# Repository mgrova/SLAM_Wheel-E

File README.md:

# SLAM_Wheel-E
Este es un proyecto en el cual se busca realizar una comparativa de diferentes técnicas de SLAM empleando un robot movil diferencial tipo Rover.

# Wheel-E 

Un análisis en detalle de todo el proyecto, así como de sus resultados se encuentra (en español) [aquí](doc.md). Los recursos bibliográficos disponibles se pueden consultar en [docs/](SLAM_Wheel-E/docs/). 

# DEPENDENCIAS
## Uso de lod gpio de la RPi
Se hace uso de la libreria pigpio:(http://abyz.me.uk/rpi/pigpio/download.html)

```
wget abyz.me.uk/rpi/pigpio/pigpio.tar
tar xf pigpio.tar
cd PIGPIO
make
sudo make install
```

## Comunicación Serial RPi-Arduino
Se hará uso de la librería de Python:

https://github.com/harmsm/PyCmdMessenger

Destacar que se emplará python2.7 y no python3.

## Comunicación multimaster(https://wiki.ros.org/multimaster_fkie)
Para comunicar la RPi y el PC, es necesario tener instalado el siguiente paquete:

```
sudo apt install ros-kinetic-multimaster-fkie
sudo apt install ros-kinetic-multimaster-launch
```

## Drivers Kinect v1 (RGB-D Camera)
Se emplearán tanto los driver necesarios para leer la IMU de la cámara y mover su motor cómo los que permiten que se pueda correr la cámara.

 - Drivers Cámara principales
```
sudo apt install ros-kinetic-freenect-stack<
```

 - Driver IMU y motor de la cámara(https://wiki.ros.org/kinect_aux)
```
sudo apt-get install libusb-1.0-0 libusb-1.0-0-dev
```
```
cd ~/catkin_ws/src
git clone https://github.com/muhrix/kinect_aux.git -b indigo
cd ~/catkin_ws
catkin_make
```

## RTAB-Map SLAM
Se deberan tener instalados los siguientes paquetes de ros y sus respectivas dependencias:
```
sudo apt-get install ros-kinetic-rtabmap-ros
sudo apt-get install ros-kinetic-octomap-*

```

## ORB-SLAM2
Se enlaza directamente al repositorio original.
https://github.com/appliedAI-Initiative/orb_slam_2_ros

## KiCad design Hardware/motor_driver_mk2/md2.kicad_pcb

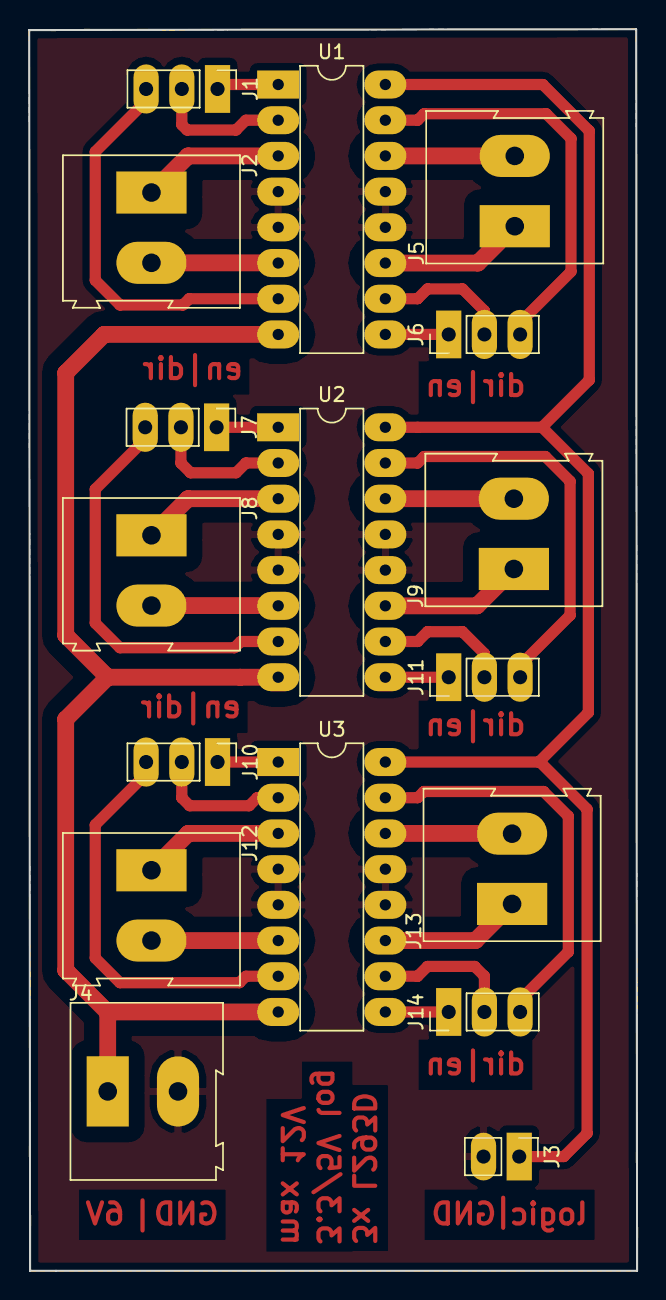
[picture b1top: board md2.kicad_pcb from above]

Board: 2 copper layers, 43.2 x 88.3 mm, 17 parts (0 on the bottom side), 32 nets.

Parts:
J1, J7, J10: mode&en M1; Pin_Header_Straight_1x03_Pitch2.54mm
J2, J8, J12: M1; TerminalBlock_Altech_AK300-2_P5.00mm
J3: Logic supply voltage; Pin_Header_Straight_1x02_Pitch2.54mm
J4: Power supply voltage; TerminalBlock_Altech_AK300-2_P5.00mm
J5, J9, J13: M2; TerminalBlock_Altech_AK300-2_P5.00mm
J6, J11, J14: mode&en M2; Pin_Header_Straight_1x03_Pitch2.54mm
U1, U2, U3: L293D; DIP-16_W7.62mm_LongPads

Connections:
/en1: J1.1, U1.1
/en2: J6.1, J14.1, U1.9, U3.9
/en12: J7.1, U2.1
/en13: J10.1, U3.1
/en22: J11.1, U2.9
/m1+: J2.1, U1.3
/m1+2: J8.1, U2.3
/m1+3: J12.1, U3.3
/m1-: J2.2, U1.6
/m1-2: J8.2, U2.6
/m1-3: J12.2, U3.6
/m2+: J5.1, U1.11
/m2+2: J9.1, U2.11
/m2+3: J13.1, U3.11
/m2-: J5.2, U1.14
/m2-2: J9.2, U2.14
/m2-3: J13.2, U3.14
/mode1+: J1.2, U1.2
/mode1+2: J7.2, U2.2
/mode1+3: J10.2, U3.2
/mode1-: J1.3, U1.7
/mode1-2: J7.3, U2.7
/mode1-3: J10.3, U3.7
/mode2+: J6.2, U1.10
/mode2+2: J11.2, U2.10
/mode2+3: J14.2, U3.10
/mode2-: J6.3, U1.15
/mode2-2: J11.3, U2.15
/mode2-3: J14.3, U3.15
GND: J3.2, J4.2, U1.4, U1.5, U1.12, U1.13, U2.4, U2.5, U2.12, U2.13, U3.4, U3.5, U3.12, U3.13
ardu5v: J3.1, U1.16, U2.16, U3.16
supply: J4.1, U1.8, U2.8, U3.8

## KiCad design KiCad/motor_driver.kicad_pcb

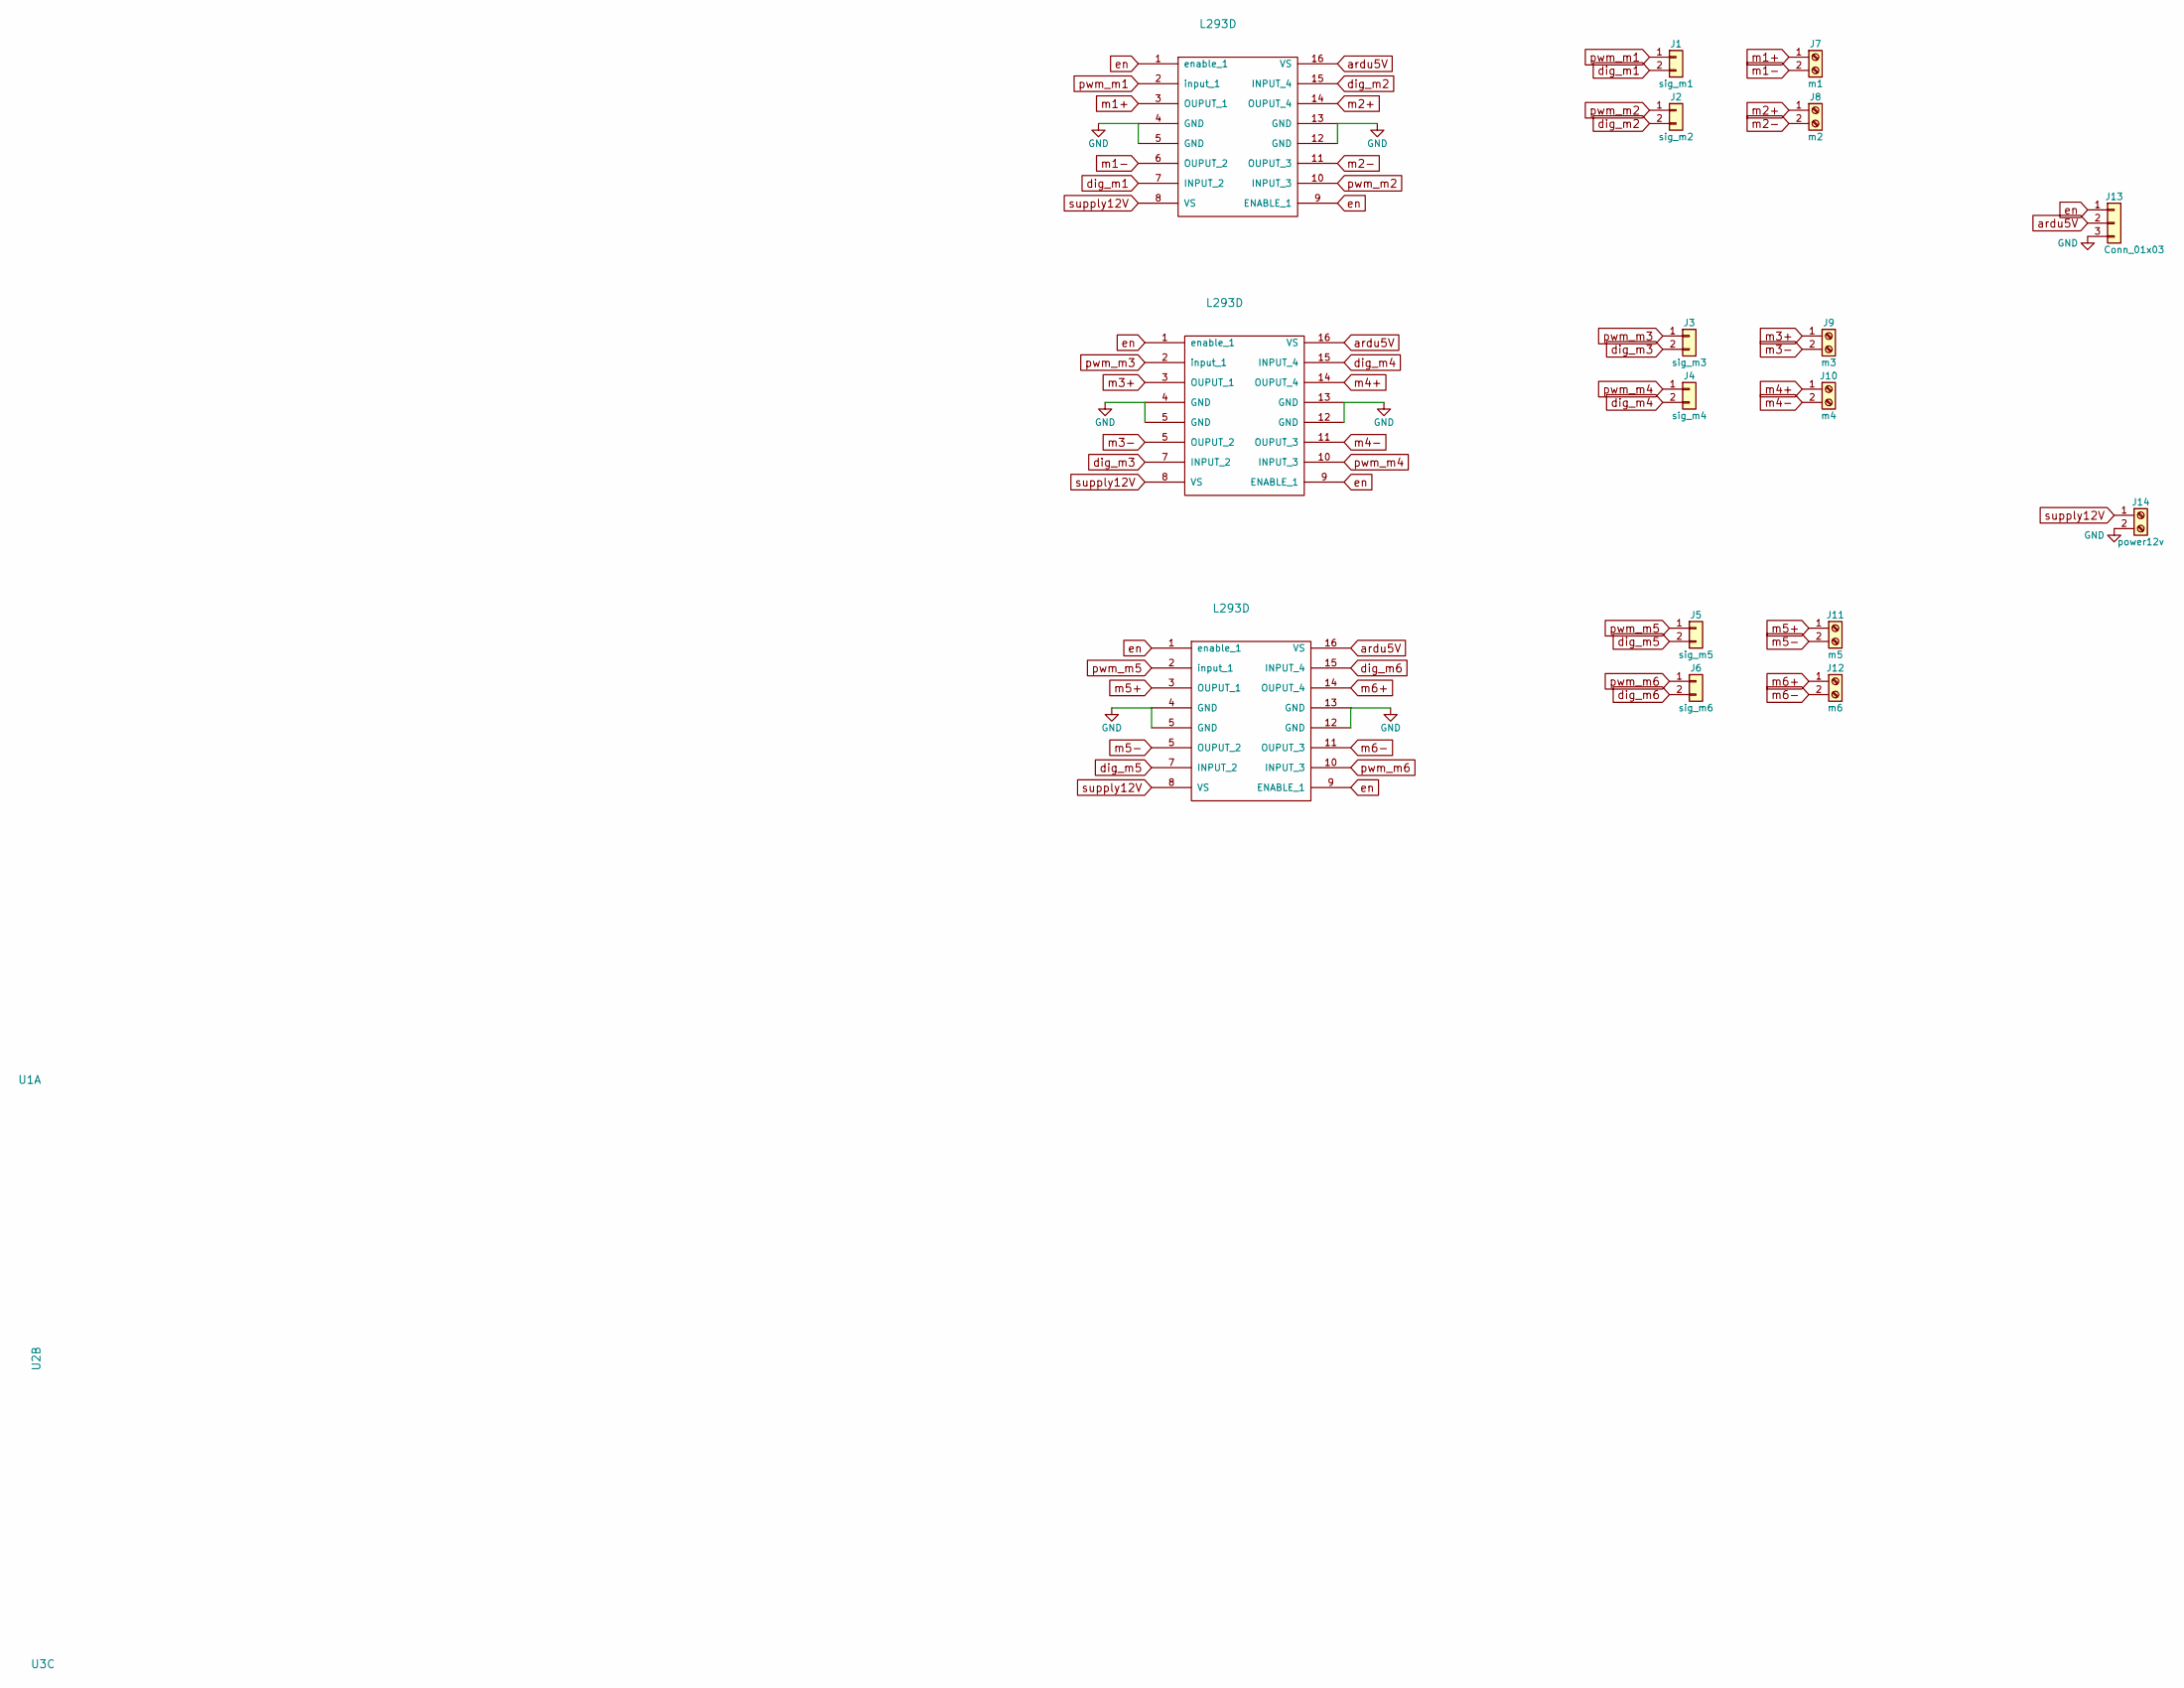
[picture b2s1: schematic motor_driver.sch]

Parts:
J1: sig_m1; Pin_Header_Straight_1x02_Pitch2.00mm
J2: sig_m2; Pin_Header_Straight_1x02_Pitch2.00mm
J3: sig_m3; Pin_Header_Straight_1x02_Pitch2.00mm
J4: sig_m4; Pin_Header_Straight_1x02_Pitch2.00mm
J5: sig_m5; Pin_Header_Straight_1x02_Pitch2.00mm
J6: sig_m6; Pin_Header_Straight_1x02_Pitch2.00mm
J7: m1; TerminalBlock_Altech_AK300-2_P5.00mm
J8: m2; TerminalBlock_Altech_AK300-2_P5.00mm
J9: m3; TerminalBlock_Altech_AK300-2_P5.00mm
J10: m4; TerminalBlock_Altech_AK300-2_P5.00mm
J11: m5; TerminalBlock_Altech_AK300-2_P5.00mm
J12: m6; TerminalBlock_Altech_AK300-2_P5.00mm
J13: Conn_01x03; Pin_Header_Straight_1x03_Pitch2.00mm
J14: power12v; TerminalBlock_Altech_AK300-2_P5.00mm
U1, U2, U3: L293D; DIP-16_W7.62mm_Socket_LongPads

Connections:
ardu5V: J13.2, U1.16 (VS), U2.16 (VS), U3.16 (VS)
dig_m1: J1.2, U1.7 (INPUT_2)
dig_m2: J2.2, U1.15 (INPUT_4)
dig_m3: J3.2, U2.7 (INPUT_2)
dig_m4: J4.2, U2.15 (INPUT_4)
dig_m5: J5.2, U3.7 (INPUT_2)
dig_m6: J6.2, U3.15 (INPUT_4)
en: J13.1, U1.1 (enable_1), U1.9 (ENABLE_1), U2.1 (enable_1), U2.9 (ENABLE_1), U3.1 (enable_1), U3.9 (ENABLE_1)
m1+: J7.1, U1.3 (OUPUT_1)
m1-: J7.2, U1.6 (OUPUT_2)
m2+: J8.1, U1.14 (OUPUT_4)
m2-: J8.2, U1.11 (OUPUT_3)
m3+: J9.1, U2.3 (OUPUT_1)
m4+: J10.1, U2.14 (OUPUT_4)
m4-: J10.2, U2.11 (OUPUT_3)
m5+: J11.1, U3.3 (OUPUT_1)
m6+: J12.1, U3.14 (OUPUT_4)
m6-: J12.2, U3.11 (OUPUT_3)
pwm_m1: J1.1, U1.2 (input_1)
pwm_m2: J2.1, U1.10 (INPUT_3)
pwm_m3: J3.1, U2.2 (input_1)
pwm_m4: J4.1, U2.10 (INPUT_3)
pwm_m5: J5.1, U3.2 (input_1)
pwm_m6: J6.1, U3.10 (INPUT_3)
supply12V: J14.1, U1.8 (VS), U2.8 (VS), U3.8 (VS)

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
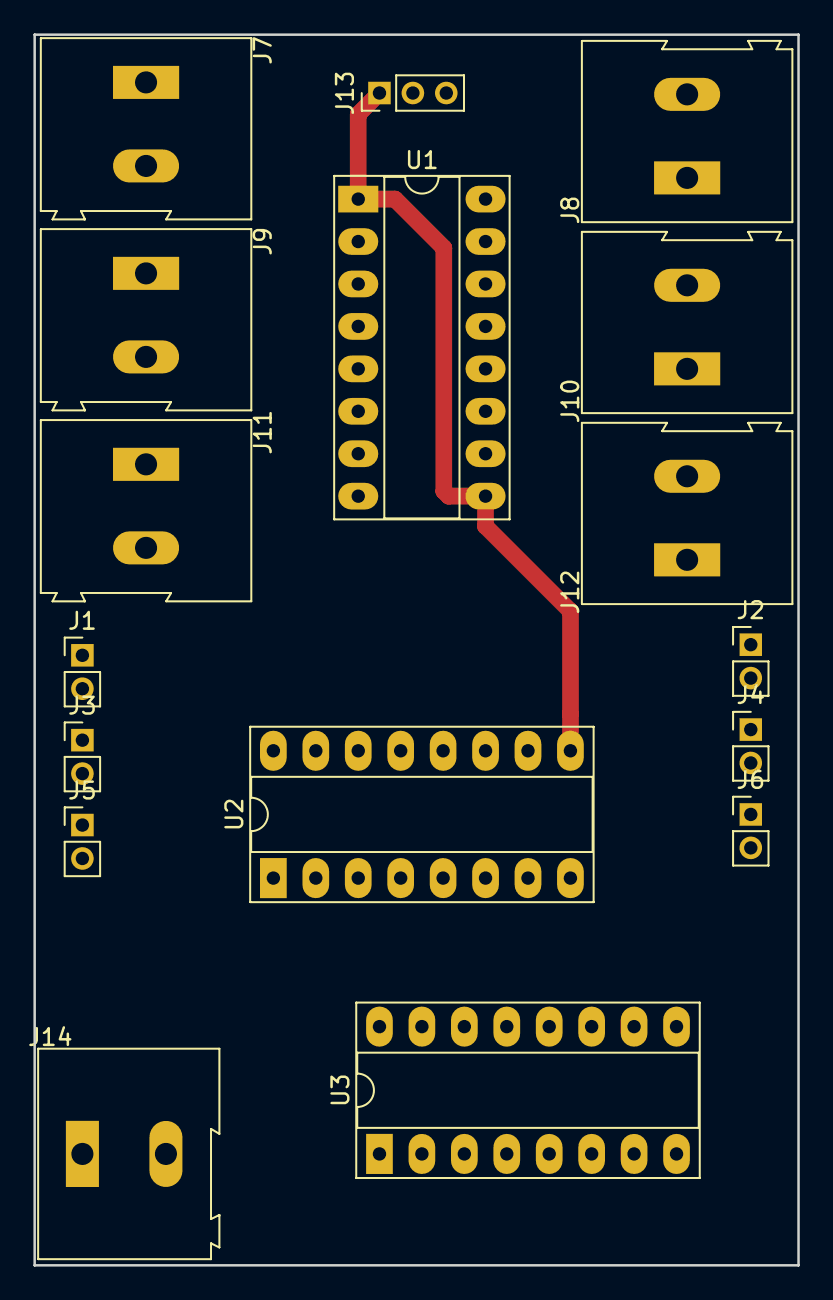
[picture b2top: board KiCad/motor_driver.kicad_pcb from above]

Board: 2 copper layers, 45.7 x 73.7 mm, 17 parts (0 on the bottom side), 28 nets.

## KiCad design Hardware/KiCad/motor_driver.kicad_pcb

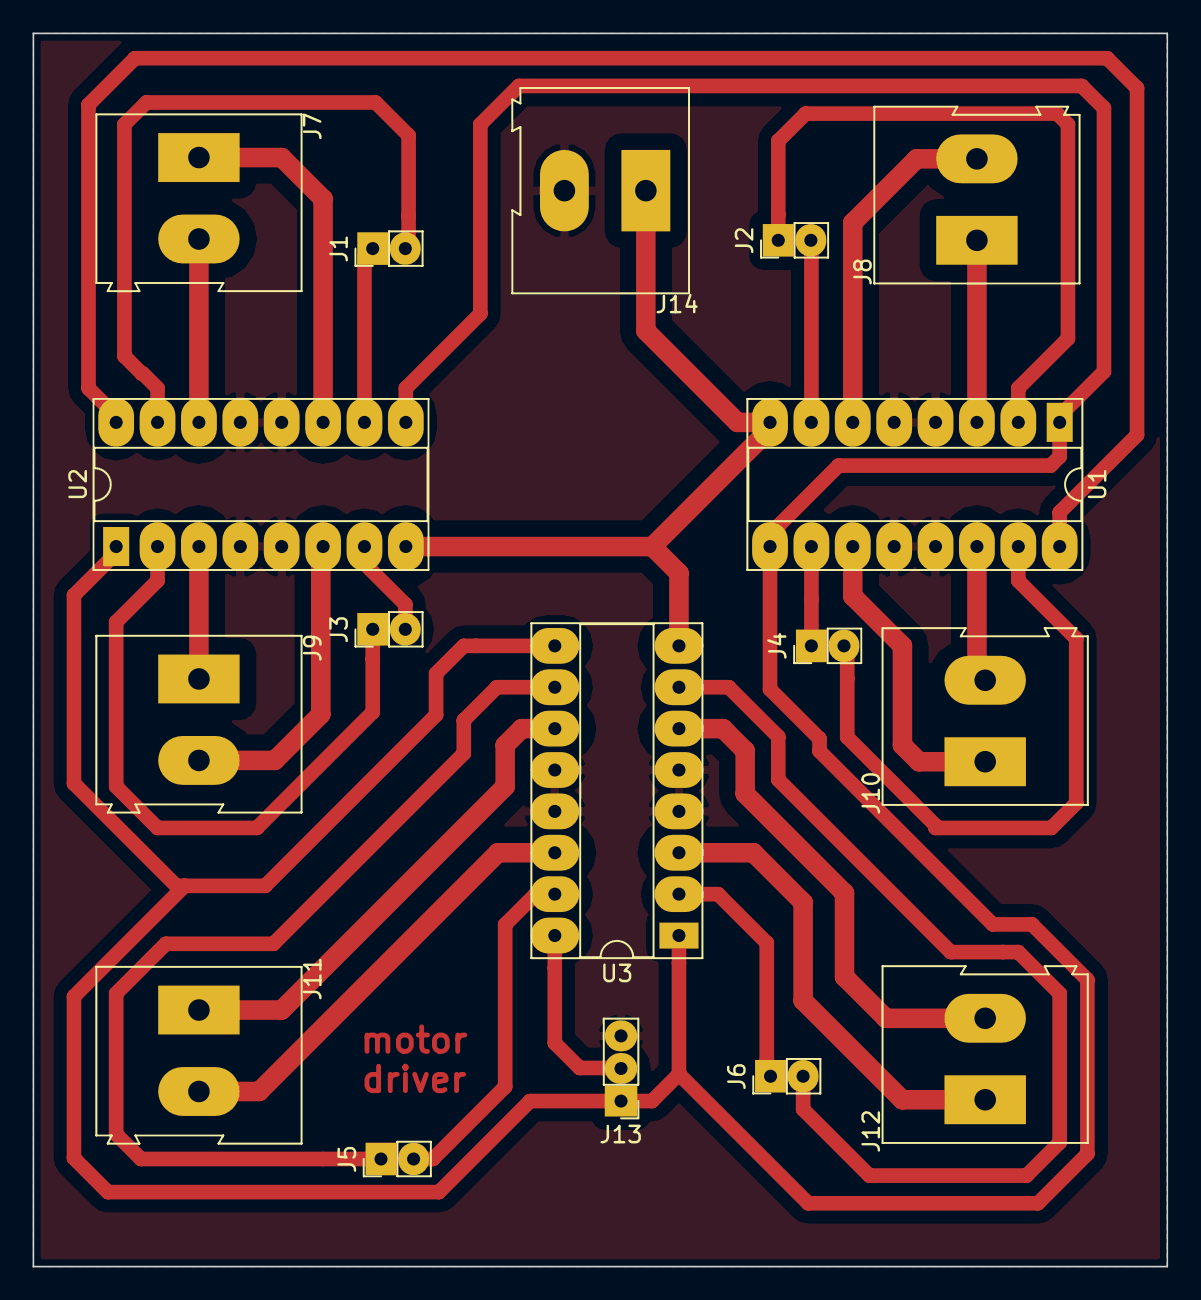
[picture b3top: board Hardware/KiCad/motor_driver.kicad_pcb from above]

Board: 2 copper layers, 69.6 x 75.7 mm, 17 parts (0 on the bottom side), 28 nets.

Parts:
J1, J2, J3, J4, J5, J6: Conn_01x02; Pin_Header_Straight_1x02_Pitch2.00mm
J7: m1; TerminalBlock_Altech_AK300-2_P5.00mm
J8: m2; TerminalBlock_Altech_AK300-2_P5.00mm
J9: m3; TerminalBlock_Altech_AK300-2_P5.00mm
J10: m4; TerminalBlock_Altech_AK300-2_P5.00mm
J11: m5; TerminalBlock_Altech_AK300-2_P5.00mm
J12: m6; TerminalBlock_Altech_AK300-2_P5.00mm
J13: Conn_01x03; Pin_Header_Straight_1x03_Pitch2.00mm
J14: power12v; TerminalBlock_Altech_AK300-2_P5.00mm
U1, U2, U3: L293D; DIP-16_W7.62mm_Socket_LongPads

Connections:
GND: J13.3, J14.2, U1.4, U1.5, U1.12, U1.13, U2.4, U2.5, U2.12, U2.13, U3.4, U3.5, U3.12, U3.13
ardu5V: J13.2, U1.16, U2.16, U3.16
dig_m1: J1.2, U2.15
dig_m2: J2.2, U1.7
dig_m3: J3.2, U2.7
dig_m4: J4.2, U1.15
dig_m5: J5.2, U3.15
dig_m6: J6.2, U3.7
en: J13.1, U1.1, U1.9, U2.1, U2.9, U3.1, U3.9
m1+: J7.1, U2.11
m1-: J7.2, U2.14
m2+: J8.1, U1.3
m2-: J8.2, U1.6
m3+: J9.1, U2.3
m3-: J9.2, U2.6
m4+: J10.1, U1.11
m4-: J10.2, U1.14
m5+: J11.1, U3.11
m5-: J11.2, U3.14
m6+: J12.1, U3.3
m6-: J12.2, U3.6
pwm_m1: J1.1, U2.10
pwm_m2: J2.1, U1.2
pwm_m3: J3.1, U2.2
pwm_m4: J4.1, U1.10
pwm_m5: J5.1, U3.10
pwm_m6: J6.1, U3.2
supply12V: J14.1, U1.8, U2.8, U3.8

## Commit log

2019-02-24 Anadido el fichero con el analisis de los diferentes metodos de slam. Tambien los datasets para slam RGB-D
2019-02-24 pcb driver motor
2019-02-24 Datasheet L293D
2019-02-25 diy l293d design in kicad
2019-02-25 one f*** layer pcb finished, with just 3 bridges
2019-02-28 Added arduino files to control motors
2019-02-28 Added RPi node to control motors with freenet launch
2019-03-01 Modified PCB and added link to txt
2019-03-01 motor driver pcb mkII
2019-03-01 added text
2019-03-01 added robot in freecad base
2019-03-01 added gitignore
2019-03-06 Motor driver mk2 pcb
2019-03-06 Added backup
2019-03-06 soldad esto si hay huevos
2019-03-08 holi
2019-03-08 added face robot to freecad filesystem and dc motors "datasheet". In slam methods octomap
2019-03-08 added arduino code working............ i guess
2019-03-08 Added 9-DOF IMU Datasheet to docs dir
2019-03-09 la placa ya no esta al reves
2019-03-09 cambiando nombres
2019-03-12 Anadido catkin al repo, de tal modo que sea posible compilar los nodos desde él. Se ha optado inicialmente por realizar una union de todos los nodos desarrollados en mismo catkin. Por otro lado, se h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
2019-03-18 ponerla wapa
2019-03-22 Arduino code with working pin-out added
2019-03-22 rm_d old code
2019-03-24 cambiados los pine
2019-03-24 new serial communication
2019-03-28 node for mpu9250 imu
2019-03-30 basic encoder code
2019-03-30 velocidad angular medida. Imagen pin out de RPi3B
2019-04-01 dynamic encoder objects creation
2019-04-01 created ros node that publish encoder read in float32. Must be tested
2019-04-01 Reverted @ f0e9ce2
2019-04-01 minor bug fixes
2019-04-01 Revert "Added comments to code. Must to review implementation of differential model of robot and the ticks transformation to vel"
    This reverts commit f0e9ce22611b0827e1cc02784050179941e1d165.
2019-04-01 Created odometry node. Must work more or less fine
2019-04-01 Added comments to code. Must to review implementation of differential model of robot and the ticks transformation to vel
2019-04-02 minor changes and code merging from ROS and RPi folders
2019-04-02 conde consistency and minor changes
2019-04-02 meh, kill me la vida papasito
2019-04-02 init control motors node
2019-04-02 el caos se ha acercado a su fin
2019-04-02 el caos, acabó. LO QUITÉ YA
2019-04-02 soy un bochachacla
2019-04-02 more things
2019-04-02 ANALISIS CONTROL MOTORES NIVELES. ME RAYA LO DEL LOW-MID-HIGH LEVEL CONTROLS
2019-04-02 cosas the in the last minutaso
2019-04-04 added class for magnetometer ak
2019-04-09 serial communication with cmdMessenger
2019-04-09 Changed package name in ROS,"wheel_encoder"->"wheele". Also, added arduino communication
2019-04-09 new node for serial communication
2019-04-09 little bugs solved
2019-04-09 Added shutdown
2019-04-09 syntaxx error
2019-04-13 Added launch to Kinect in RPi to wheele package. Modification of readme with dependencies too
2019-04-13 Added launch to init multimaster in RPi or PC in function of an "using_rpi" argument
2019-04-13 solved errors in launch. Added data_skip argument when launch libfreenect
2019-04-13 solved finish bugs. Launch working fine
2019-04-14 Anadido el control con el mando. Ademas de ello partes para la simulacion en gazebo. mas movidad que no recuerdo
2019-04-14 Solventado bug en el calculo de la velocidad para la comunicacion serie
2019-04-14 Modifiacion de la lectura para que meustre de tieso que lee todos los encoders, he comentado la creacion dinamica de los objetos y lo he hecho de tieso a manopla
2019-04-15 Muestreo de los ticks para la caracteristica estatica
2019-04-15 Errores en el codigo y caracteristica estatica en ticks.txt
2019-04-15 he intentado hacer el control y he muerto en el intento
2019-04-18 Finished imu
2019-04-18 Added continuos read mode
2019-04-18 publsh imu and mangetometer data
2019-04-22 minor chagnge at .gitingore
2019-04-22 got rmd file back hu3hu3hu3
2019-04-28 Modificaciones de los launch de conexion multimaster. Se acabo el zeroconf. Tambien los yaml de config de wheele
2019-04-28 little bugs
2019-04-28 depth rtabmap working. orb2 testing
2019-04-30 deberia tirar el orb_slam2 monocular
2019-04-30 anadido los configs para rviz mono
2019-04-30 ficheros de configuracio nde rviz para octomap
2019-04-30 cosas han pasado here it is an experimento
2019-05-01 control experiment static characterisctic
2019-05-01 minor changes
2019-05-01 bug fixed
2019-05-02 pwm6 msg
2019-05-02 include pwm6
2019-05-02 lo del topico de lo de los ticks y eso
2019-05-02 cosas de calibrar jejeXD
2019-05-02 stl encoder file
2019-05-02 edit of .gitignore
2019-05-02 data types fixed
2019-05-02 arduino error
2019-05-02 saturation added
2019-05-02 *.launch edtd to rel paths to wheele
2019-05-02 lo de la velosidad 0 y eso
2019-05-02 estamos en ello
2019-05-02 experimento realizado
2019-05-03 cosillas de control 1
2019-05-03 cosillas de los pkg
2019-05-05 control que no se si tira
2019-05-05 jaja git es mi mdropboc
2019-05-05 paralelolo lololo lolo lolo lolololo
2019-05-06 ya no se ni lo que mergeo
2019-05-06 pid paralelololo a ojojojojo
2019-05-06 pid subscriber
2019-05-06 saber interpretar polos y ceros en bucle cerrado a ojo sobre el plano imaginario discreto para tunear pid a mano kp=0.14 ki=0.2 o mas en vd da un poco igual
2019-05-06 barriendo
2019-05-06 6 controles
2019-05-06 6 controles que compilan
2019-05-08 added 6 control in the worst way
2019-05-08 encoder stl adapted
2019-05-08 fixed little bug
2019-05-08 launch wheele
2019-05-08 m1l setup
2019-05-08 zero vel at wheel_encoder
2019-05-08 fixeando en 1 link hd no fake
2019-05-08 wheel_ecoder.cpp patch
2019-05-08 modification rtabmap
2019-05-08 minor fix
2019-05-08 encoder.cpp patch --status:=WORKING
2019-05-08 Added fake laser-scan to rtabmap
2019-05-08 changed vars from float to double
2019-05-08 encoder status: SWEEEEEET
2019-05-08 Added dynamic reconfig control parameters
2019-05-08 baia baia
2019-05-08 ahi seguimos. Modificando un poco el codigo del control
2019-05-08 control changes
2019-05-08 Publishing error to can know what fckin is happening
2019-05-08 se grafican las lecturas de los encoders con rqt_plot
2019-05-08 lo ultimo que toque de la clase re_decoder antes de irme
2019-05-09 filtrado de velocidad. Sin probar
2019-05-09 Tuneados 3 controladores. Cambia el rango de referenca
2019-05-09 Modificados parametros del control
2019-05-12 little a little
2019-05-12 control in cb
2019-05-12 test i rpi
2019-05-12 claw bf cb
2019-05-12 changed declaration place of dt
2019-05-14 lo del otro dia. Modificado serial
2019-05-14 optimization slam in rpi
2019-05-14 changes in pc
2019-05-14 workin
2019-05-17 atmega2560 code
2019-05-17 added cmdMessages to src/serial_com.py and Arduino/mega/main.cpp
2019-05-17 modified little error
2019-05-17 YAML to configure EKF example copied. Time to modified it
2019-05-18 mega code
2019-05-18 Setup of EKFs .yaml config file
2019-05-20 Arduino mega code
2019-05-20 serial & encoders fixes
2019-05-21 new branch
2019-05-21 changed com. Time to fix odom
2019-05-21 Added rosbag with ticks to test odometry node
2019-05-21 Odometry node working done. Problems with m/s to rad/s solved... I think so
2019-05-22 Imu calibrated. Madgwick filter running. There is a bag to see the result. Must be retuned the caliration.
2019-05-22 modifications of things
2019-05-23 creo que ahora si hay signo en las velocidades jejeje
2019-05-25 imu data published in base_link frame
2019-05-26 modificado .gitignore
2019-05-26 Configuration files camera
2019-05-26 added robot_localization
2019-05-26 modificado launch de freenekt para encontrar lo de lacamra
2019-05-26 nodo de odometria arreglado
2019-05-26 base-link to imu-link
2019-06-04 Added project memory base
2019-06-05 Added RTAB-Map theory to project memory
2019-06-05 resolution changed from 488 to 480
2019-06-05 stable
2019-06-05 finding stable situation
2019-06-05 cosas de bibliografia
2019-06-05 jeje xddd
2019-06-05 intro hecha
2019-06-06 Added theory ORB-SLAM2
2019-06-06 excluded .synctext.gz latex files
2019-06-06 intro+hw
2019-06-06 chasis + cosas en latex/sofware. correciones generales en el doc
2019-06-07 hw y tal. sere imbecil pero no consigo añadir una referencia
2019-06-07 una fotico guapa pal tinder
2019-06-08 Added octomap and SLAM things. Time to introduce experiments
2019-06-08 Added all SLAM images and comparation between them
2019-06-08 escrito hasta la odometria en la memoria
2019-06-08 cosas de las cosas fisicas
2019-06-09 cosas de las blandas
2019-06-09 [mensaje generico aqui]
2019-06-09 Añadido teoria slam y algo software
2019-06-09 jeje
2019-06-09 mas cosas
2019-06-09 al carajo el gato
2019-06-10 Cositas
2019-06-10 foto ard
2019-06-10 filtro en ello
2019-06-10 Added octomap picture
2019-06-10 ekf,arduino, y revision hasta ekf
2019-06-10 Code cleaned
2019-06-10 Cosas
2019-06-10 corregidas las faltas
2019-06-10 finiquito
2020-01-14 Added detailed explanation pdf to root for visibility
2020-01-14 Añadido fotos y links
